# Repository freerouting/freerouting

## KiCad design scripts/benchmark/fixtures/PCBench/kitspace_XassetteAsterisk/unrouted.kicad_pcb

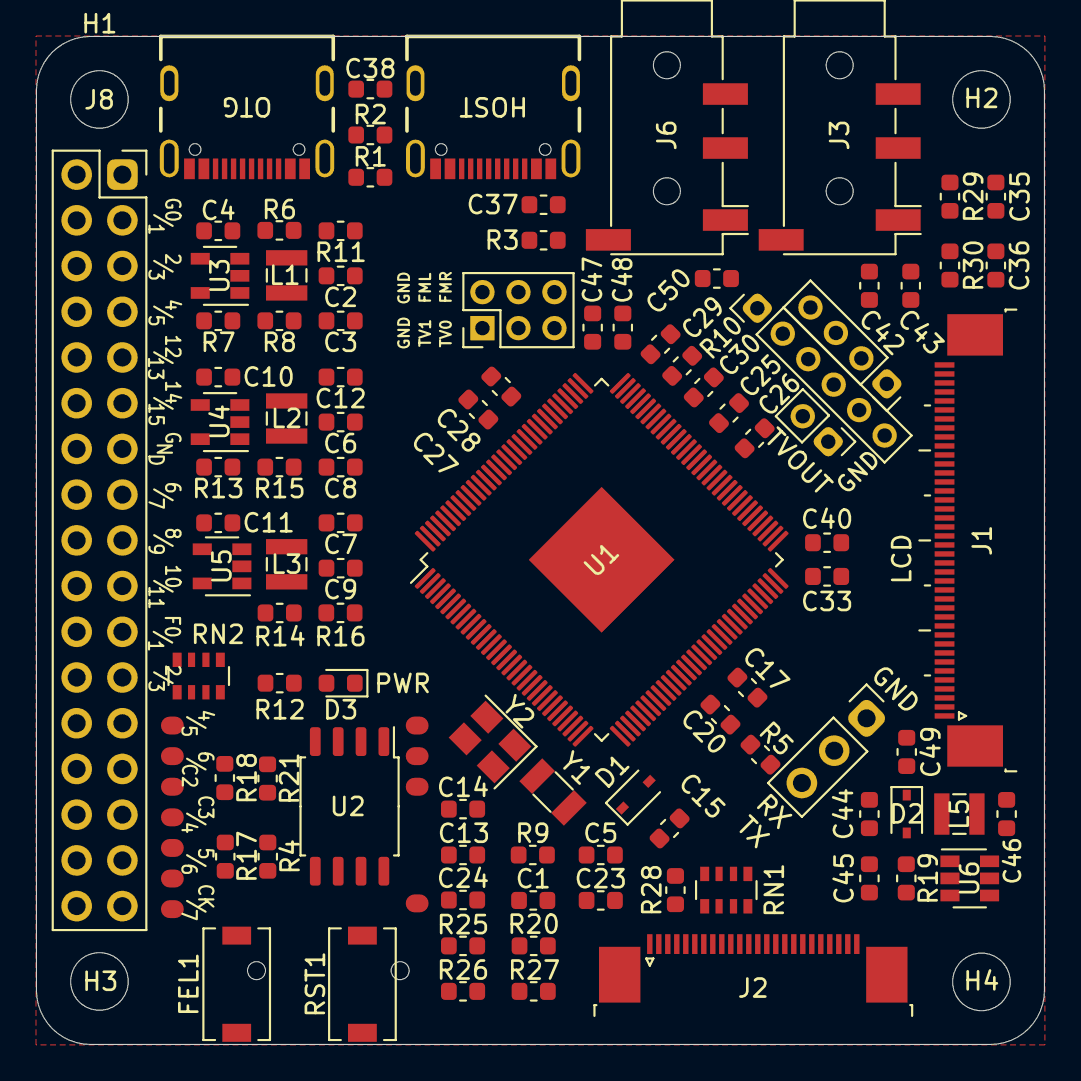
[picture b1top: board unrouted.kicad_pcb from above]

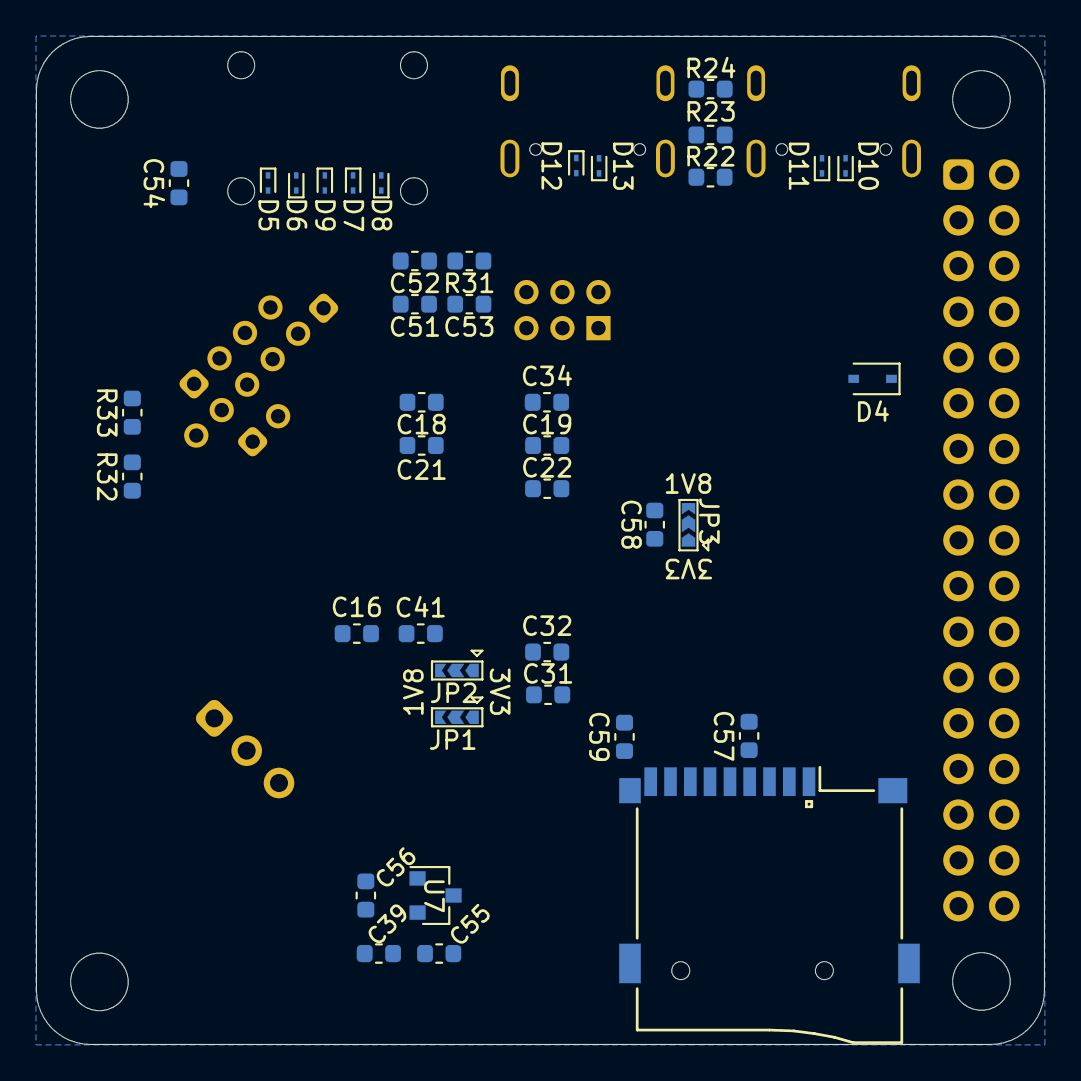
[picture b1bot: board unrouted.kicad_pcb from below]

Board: 2 copper layers, 56.0 x 56.0 mm, 145 parts (41 on the bottom side), 151 nets, no tracks yet.

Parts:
C1, C5, C13, C14: 18p; C_0603_1608Metric
C2, C4, C6, C7, C10, C11, C37, C38, C44, C46, C53, C55: 10u; C_0603_1608Metric
C3, C8, C9, C12, C15, C16, C17, C18, C19, C20, C21, C22, C23, C24, C25, C26, C31, C32, C33, C34, C35, C36, C39, C40, C41, C42, C43, C45, C47, C48, C49, C50, C51, C54, C56, C57, C58, C59: 0.1u; C_0603_1608Metric
C27, C28: 1u; C_0603_1608Metric
C29, C30: 0.47u; C_0603_1608Metric
C52: 33p; C_0603_1608Metric
D1, D2, D4: D; D_SOD-323
D3: LED; LED_0603_1608Metric
D5, D6, D7, D8, D9, D10, D11, D12, D13: ESD9B3.3ST5G; D_SOD-923
FEL1: SW_SPST; SW_SPST_EVQPE1
H1, H2, H3, H4: MountingHole; MountingHole_3.2mm_M3
H5: MountingHole_Pad; SolderWirePad_1x01_SMD_5x10mm
J1: Conn_01x40_MountingPin; TE_4-1734839-0_1x40-1MP_P0.5mm_Horizontal
J2: Conn_01x24_MountingPin; TE_2-1734839-4_1x24-1MP_P0.5mm_Horizontal
J3, J6: AudioJack4; Jack_3.5mm_PJ320D_Horizontal
J4, J5: USB4105-GF-A; GCT_USB4105-GF-A
J7: Conn_01x04; PinSocket_1x04_P2.00mm_Vertical
J8: Conn_02x17_Odd_Even; PinSocket_2x17_P2.54mm_Vertical
J9: Conn_01x06; PinHeader_1x06_P2.00mm_Vertical
J10: Conn_02x03_Odd_Even; PinHeader_2x03_P2.00mm_Vertical
J11: Conn_01x02; PinHeader_1x02_P2.00mm_Vertical
J12: Conn_01x03; PinHeader_1x03_P2.54mm_Vertical
J13: RTL8189FTV_Mod; 8189Mod
JP1, JP2, JP3: Jumper_3_Open; SolderJumper-3_P2.0mm_Open_TrianglePad1.0x1.5mm
L1, L2, L3: 2.2u; L_Wuerth_MAPI-2510
L5: 10u; L_Wuerth_MAPI-2510
R1, R2, R3, R12, R22, R23, R24: 5.1k; R_0603_1608Metric
R4, R11, R17, R18, R21, R25, R26, R27, R28, R32, R33: 10k; R_0603_1608Metric
R5: 240; R_0603_1608Metric
R6: 1k; R_0603_1608Metric
R7: 15k; R_0603_1608Metric
R8: 68k; R_0603_1608Metric
R9: 10M; R_0603_1608Metric
R10: 0; R_0603_1608Metric
R13, R16, R20: 100k; R_0603_1608Metric
R14, R15: 200k; R_0603_1608Metric
R19, R29, R30: 2R2; R_0603_1608Metric
R31: 2.2k; R_0603_1608Metric
RN1, RN2: R_Pack04; R_Array_Convex_4x0603
RST1: SW_SPST; SW_SPST_EVQPE1
Ref**: Val**; rvlogo_inv
U1: F133; LQFP-128_14x14mm_P0.4mm
U2: W25Q32JVSS; SOIC-8_5.23x5.23mm_P1.27mm
U3, U4, U5: SY8089AAAC; SOT-23-5
U6: SY7201ABC; SOT-23-6
U7: XC6206PxxxMR; SOT-23
XS1: uSD_SMD; Conn_uSDcard
Y1: Crystal; Crystal_SMD_3215-2Pin_3.2x1.5mm
Y2: 24M; Crystal_SMD_3225-4Pin_3.2x2.5mm

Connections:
+1V8: C6.1, C8.1, C17.1, C18.1, C19.1, C31.1, C32.1, C33.1, C34.1, C53.1, JP1.3, JP2.3, JP3.3, L2.1, R15.1, R31.1, U1.20, U1.26, U1.50, U1.65, U1.89, U1.97, U1.107
+3V3: C2.1, C3.1, C15.1, C24.1, C25.1, C26.1, C49.1, C55.2, C57.1, C59.1, D1.2, D4.2, J1.4, J8.2, J13.11, J13.12, J13.13, JP1.1, JP2.1, JP3.1, L1.1, R4.1, R8.1, R11.1, R12.1, R18.1, R20.1, R25.1, R27.1, R32.1, RN2.1, RN2.2, RN2.3, U1.77, U1.83, U2.8, U7.3, XS1.4
+5V: C4.1, C10.1, C11.1, C37.1, C38.1, C46.1, D4.1, J4.A4_B9, J4.B4_A9, J5.A4_B9, J5.B4_A9, J8.1, L5.1, R2.1, R3.1, R6.1, R23.1, R24.1, U3.4, U4.4, U5.4, U6.6
/CLKO: J8.33, U1.21
/CSI-AVDD: C39.1, J2.9, J2.10, U1.28
/CSI-DVDD: C56.1, J2.8, U7.2
/CSI-IOVDD: J2.23, J2.24, JP1.2, U1.34
/CSI-PWDN: J2.5, R25.2, R26.1
/CSI-RST#: J2.4, R27.2, R28.1
/DISP: J1.31, R32.2, R33.1
/DXIN: C13.2, U1.23, Y2.1
/DXOUT: C14.1, U1.22, Y2.3
/FMINL: J10.6, U1.94
/FMINR: J10.4, U1.93
/GPADC0: J9.1, U1.101
/HPOUTFB: C54.1, U1.100
/HPOUTL: C43.2, R30.2, U1.99
/HPOUTR: C42.2, R29.2, U1.98
/HS_MIC: C50.2, C52.1, D9.2, J3.S, R31.2
/LCD0-CLK: J1.30, U1.75
/LCD0-D0: J1.5, U1.86
/LCD0-D1: J1.6, U1.85
/LCD0-D2: J1.7, U1.55
/LCD0-D3: J1.8, U1.56
/LCD0-D4: J1.9, U1.57
/LCD0-D5: J1.10, U1.58
/LCD0-D6: J1.11, U1.59
/LCD0-D7: J1.12, U1.60
/LCD0-D8: J1.13, U1.84
/LCD0-D9: J1.14, U1.82
/LCD0-D10: J1.15, U1.61
/LCD0-D11: J1.16, U1.62
/LCD0-D12: J1.17, U1.63
/LCD0-D13: J1.18, U1.64
/LCD0-D14: J1.19, U1.67
/LCD0-D15: J1.20, U1.68
/LCD0-D16: J1.21, U1.80
/LCD0-D17: J1.22, U1.79
/LCD0-D18: J1.23, U1.70
/LCD0-D19: J1.24, U1.69
/LCD0-D20: J1.25, U1.71
/LCD0-D21: J1.26, U1.72
/LCD0-D22: J1.27, U1.73
/LCD0-D23: J1.28, U1.74
/LCD0-DE: J1.34, U1.76
/LCD0-HSYNC: J1.32, U1.54
/LCD0-VSYNC: J1.33, U1.53
/LCD0_PWM: U1.52, U6.4
/LCD_A: C44.1, C45.1, D2.1, J1.2, U6.5
/LCD_K: J1.1, R19.1, U6.3
/LDOB-OUT: C41.1, U1.30, U1.48, U1.49
/LINEL: C47.2, U1.96
/LINER: C48.2, U1.95
/MIC3N: C51.1, U1.88
/MIC3P: C50.1, U1.87
/NCSI0-D0: J2.22, U1.43
/NCSI0-D1: J2.21, U1.42
/NCSI0-D2: J2.20, U1.41
/NCSI0-D3: J2.19, U1.40
/NCSI0-D4: J2.18, U1.39
/NCSI0-D5: J2.17, U1.38
/NCSI0-D6: J2.16, U1.37
/NCSI0-D7: J2.15, U1.36
/NCSI0-HSYNC: RN1.7, U1.44
/NCSI0-MCLK: J12.2, RN1.5, U1.33
/NCSI0-PCLK: J12.3, RN1.6, U1.35
/NCSI0-VSYNC: RN1.8, U1.45
/PC2: J8.28, J13.6, U1.19, U2.6
/PC3: J8.29, J13.1, RN2.8, U1.18, U2.1
/PC4: J8.30, J13.3, R4.2, R17.1, U1.17, U2.5
/PC5: FEL1.2, J8.31, J13.4, R18.2, R21.1, U1.16, U2.2
/PC6: J8.32, J13.5, U1.15, U2.3
/PC7: J8.34, J13.2, U1.14, U2.7
/PF0: J8.21, U1.7, XS1.8
/PF1: J8.22, U1.8, XS1.7
/PF2: J8.23, U1.9, XS1.5
/PF3: J8.24, RN2.6, U1.10, XS1.3
/PF4: J8.25, U1.11, XS1.2
/PF5: J8.26, U1.12, XS1.1
/PF6: J8.27, RN2.7, U1.13, XS1.9
/PG0: J8.3, U1.120
/PG1: J8.4, U1.118
/PG2: J8.5, U1.119
/PG3: J8.6, U1.121
/PG4: J8.7, U1.123
/PG5: J8.8, U1.122
/PG6: J8.15, U1.1
/PG7: J8.16, U1.2
/PG8: J8.17, U1.3
/PG9: J8.18, U1.4
/PG10: J8.19, U1.5
/PG11: J8.20, U1.6
/PG12: J8.9, U1.124
/PG13: J8.10, U1.125
/PG14: J8.11, U1.126
/PG15: J8.12, U1.127
/RST: C23.1, R20.2, RST1.2, U1.27
/TP_X1: J9.2, U1.102
/TP_X2: J9.3, U1.103
/TP_Y1: J9.4, U1.104
/TP_Y2: J9.5, U1.105
/TVIN0: J10.5, U1.108
/TVIN1: J10.3, U1.109
/TVOUT: J11.2, U1.78
/TWI2-SCK: J2.3, U1.32
/TWI2-SDA: J2.2, U1.31
/USB0_N: D11.2, J4.A7, J4.B7, U1.114
/USB0_P: D10.2, J4.A6, J4.B6, U1.115
/USB1_N: D13.2, J5.A7, J5.B7, U1.113
/USB1_P: D12.2, J5.A6, J5.B6, U1.112
/VCC_PD: C40.2, JP2.2, U1.66
/VCC_PG: C58.2, JP3.2, U1.128
/VDD-CORE: C7.1, C9.1, C16.1, C20.1, C21.1, C22.1, L3.1, R16.1, U1.46, U1.51, U1.81, U1.116, U1.117
GND: C1.2, C2.2, C3.2, C4.2, C5.2, C6.2, C7.2, C8.2, C9.2, C10.2, C11.2, C12.2, C13.1, C14.2, C15.2, C16.2, C17.2, C18.2, C19.2, C20.2, C21.2, C22.2, C23.2, C24.2, C25.2, C26.2, C27.2, C28.2, C29.1, C30.1, C31.2, C32.2, C33.2, C34.2, C35.1, C36.1, C37.2, C38.2, C39.2, C40.1, C41.2, C44.2, C45.2, C46.2, C49.2, C51.2, C52.2, C53.2, C54.2, C55.1, C56.2, C57.2, C58.1, C59.2, D3.1, D5.1, D6.1, D7.1, D8.1, D9.1, D10.1, D11.1, D12.1, D13.1, FEL1.1, H5.1, J1.3, J1.29, J1.36, J1.MP, J2.1, J2.11, J2.14, J2.MP, J3.R2, J4.A1_B12, J4.B1_A12, J4.S1, J4.S2, J4.S3, J4.S4, J5.A1_B12, J5.B1_A12, J5.S1, J5.S2, J5.S3, J5.S4, J6.R2, J8.13, J8.14, J9.6, J10.1, J10.2, J11.1, J12.1, J13.7, J13.8, R1.2, R5.2, R7.2, R10.1, R13.2, R14.2, R17.2, R19.2, R21.2, R22.2, R26.2, R28.2, R33.2, RN2.4, RN2.5, RST1.1, U2.4, U3.2, U4.2, U5.2, U6.2, U7.1, XS1.6, Y2.2, Y2.4
unnamed: C1.1, R9.1, U1.24, Y1.1
unnamed: C5.1, R9.2, U1.25, Y1.2
unnamed: C12.1, R11.2, U4.1, U5.1
unnamed: C27.1, U1.111
unnamed: C28.1, U1.110
unnamed: C29.2, U1.92
unnamed: C30.2, U1.90
unnamed: C35.2, R29.1
unnamed: C36.2, R30.1
unnamed: C42.1, D6.2, J3.R1
unnamed: C43.1, D5.2, J3.T
unnamed: C47.1, D8.2, J6.R1
unnamed: C48.1, D7.2, J6.T
unnamed: D1.1, U1.29
unnamed: D2.2, L5.2, U6.1
unnamed: D3.2, R12.2
unnamed: J1.37, J7.1
unnamed: J1.38, J7.2
unnamed: J1.39, J7.3
unnamed: J1.40, J7.4
unnamed: J2.6, RN1.1
unnamed: J2.7, RN1.2
unnamed: J2.12, RN1.3
unnamed: J2.13, RN1.4
unnamed: J4.A5, R1.1, R2.2
unnamed: J4.B5, R22.1, R23.2
unnamed: J5.A5, R3.2
unnamed: J5.B5, R24.2
unnamed: L1.2, U3.3
unnamed: L2.2, U4.3
unnamed: L3.2, U5.3
unnamed: R5.1, U1.47
unnamed: R6.2, U3.1
unnamed: R7.1, R8.2, U3.5
unnamed: R10.2, U1.91
unnamed: R13.1, R15.2, U4.5
unnamed: R14.1, R16.2, U5.5

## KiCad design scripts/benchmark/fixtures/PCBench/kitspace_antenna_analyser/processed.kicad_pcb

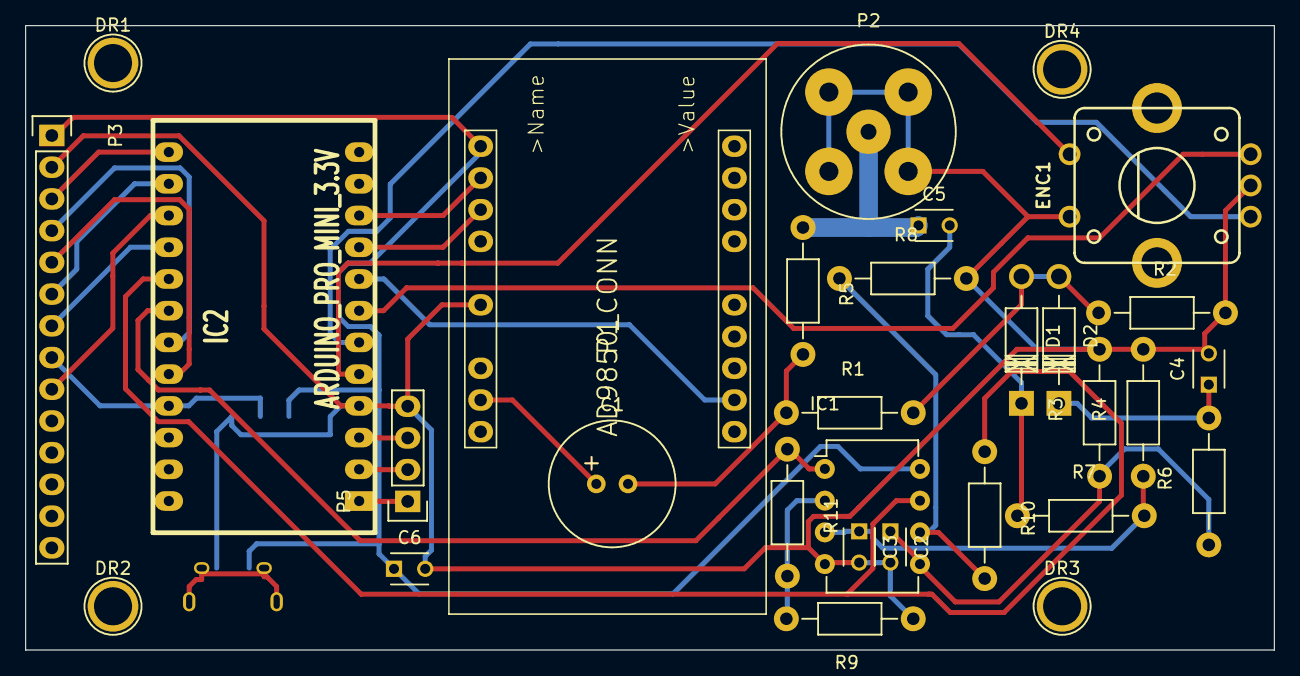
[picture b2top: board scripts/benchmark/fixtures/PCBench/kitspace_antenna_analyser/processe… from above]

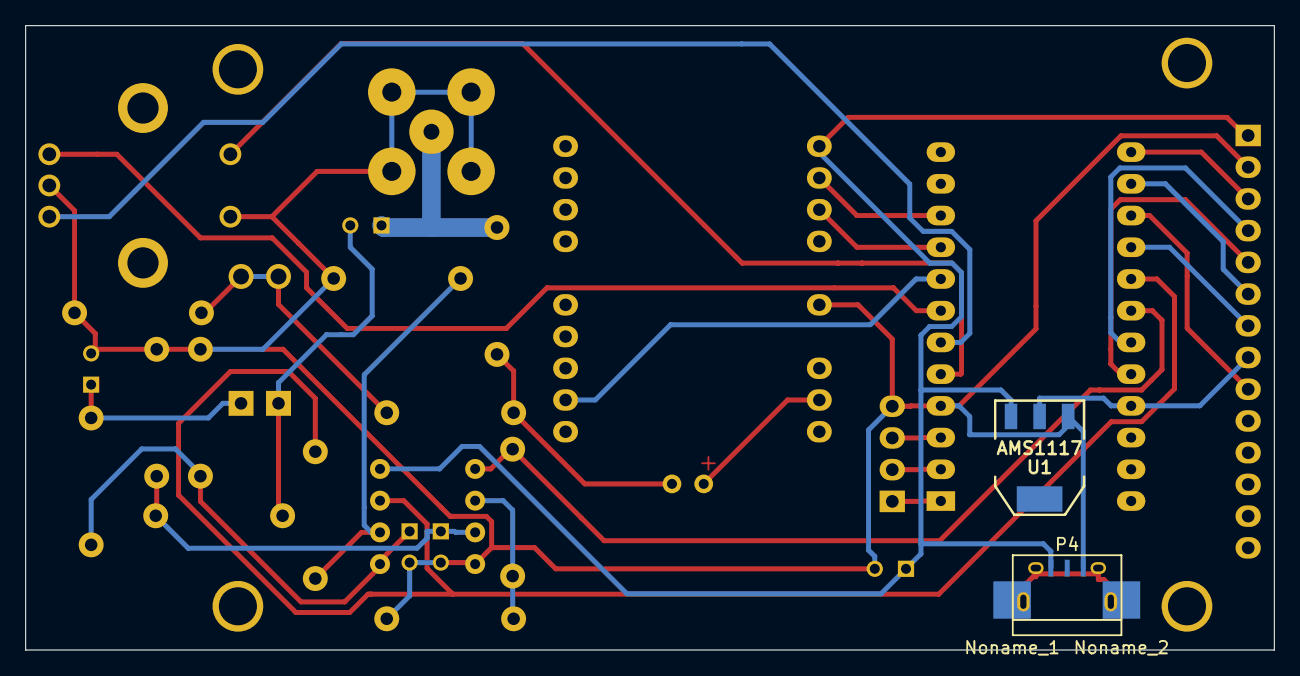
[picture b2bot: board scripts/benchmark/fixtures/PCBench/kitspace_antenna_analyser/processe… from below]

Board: 2 copper layers, 100.0 x 50.0 mm, 34 parts (4 on the bottom side), 30 nets.

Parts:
C1: 1uF; Elko_vert_20x10mm_RM2.5
C2, C3, C6: 10n; C_Disc_D3_P2.5
C4, C5: 100n; C_Disc_D3_P2.5
D1, D2: AA143; Diode_DO-41_SOD81_Horizontal_RM10
DR1, DR2, DR3, DR4: 1pin
ENC1: BI_EN11-HSM1AF15; BI_EN12-HS22AF30
IC1: MCP6002; DIP-8_W7.62mm
IC2: ARDUINO_PRO_MINI_3.3V; ARDUINO_PRO_MINI
Noname_1: S; Measurement_Point_Square-SMD-Pad_Big
Noname_2: Measurement_Point_Square-SMD-Pad_Big
P1: AD9850_CONN; DDS_AD9850
P2: BNC; bnc-ci
P3: CONN_LCD; Socket_Strip_Straight_1x14
P4: USB_OTG; USB_Micro-B
P5: CONN_PROG; Socket_Strip_Straight_1x04
R1, R2, R5: 50; Resistor_Horizontal_RM10mm
R3, R4: 100k; Resistor_Horizontal_RM10mm
R6, R7: 10k; Resistor_Horizontal_RM10mm
R8, R9: 648; Resistor_Horizontal_RM10mm
R10, R11: 5k; Resistor_Horizontal_RM10mm
U1: AMS1117; SOT223

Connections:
+5V: C6.1, IC1.8, P1.1, P3.1, P4.1, U1.3
GND: C2.2, C3.2, C4.2, C6.2, ENC1.C, ENC1.SW1, IC1.4, IC2.4, P1.6, P2.2, P3.2, P4.5, P5.4, R2.2, R3.2, R4.2, R8.2, R9.1, U1.1
unnamed: C1.1, P1.9
unnamed: C1.2, R1.1, R5.2
unnamed: C2.1, IC1.5, R3.1, R6.1
unnamed: C3.1, IC1.3, R4.1, R7.2
unnamed: C4.1, D2.1, R6.2
unnamed: C5.1, P2.1, R5.1
unnamed: C5.2, D1.1, R7.1
unnamed: D1.2, D2.2, R1.2, R2.1
unnamed: ENC1.A, IC2.6
unnamed: ENC1.B, IC2.7
unnamed: ENC1.SW2, IC2.5
unnamed: IC1.1, IC2.18, R11.1
unnamed: IC1.2, R9.2, R11.2
unnamed: IC1.6, R8.1, R10.2
unnamed: IC1.7, IC2.17, R10.1
unnamed: IC2.1, P5.1
unnamed: IC2.2, P5.2
unnamed: IC2.3, P5.3
unnamed: IC2.8, P1.12
unnamed: IC2.9, P1.3
unnamed: IC2.10, P1.2
unnamed: IC2.13, P3.3
unnamed: IC2.14, P3.6
unnamed: IC2.15, P3.9
unnamed: IC2.16, P3.7
unnamed: IC2.19, P3.4
unnamed: IC2.20, P3.5
unnamed: IC2.21, P3.8, U1.2

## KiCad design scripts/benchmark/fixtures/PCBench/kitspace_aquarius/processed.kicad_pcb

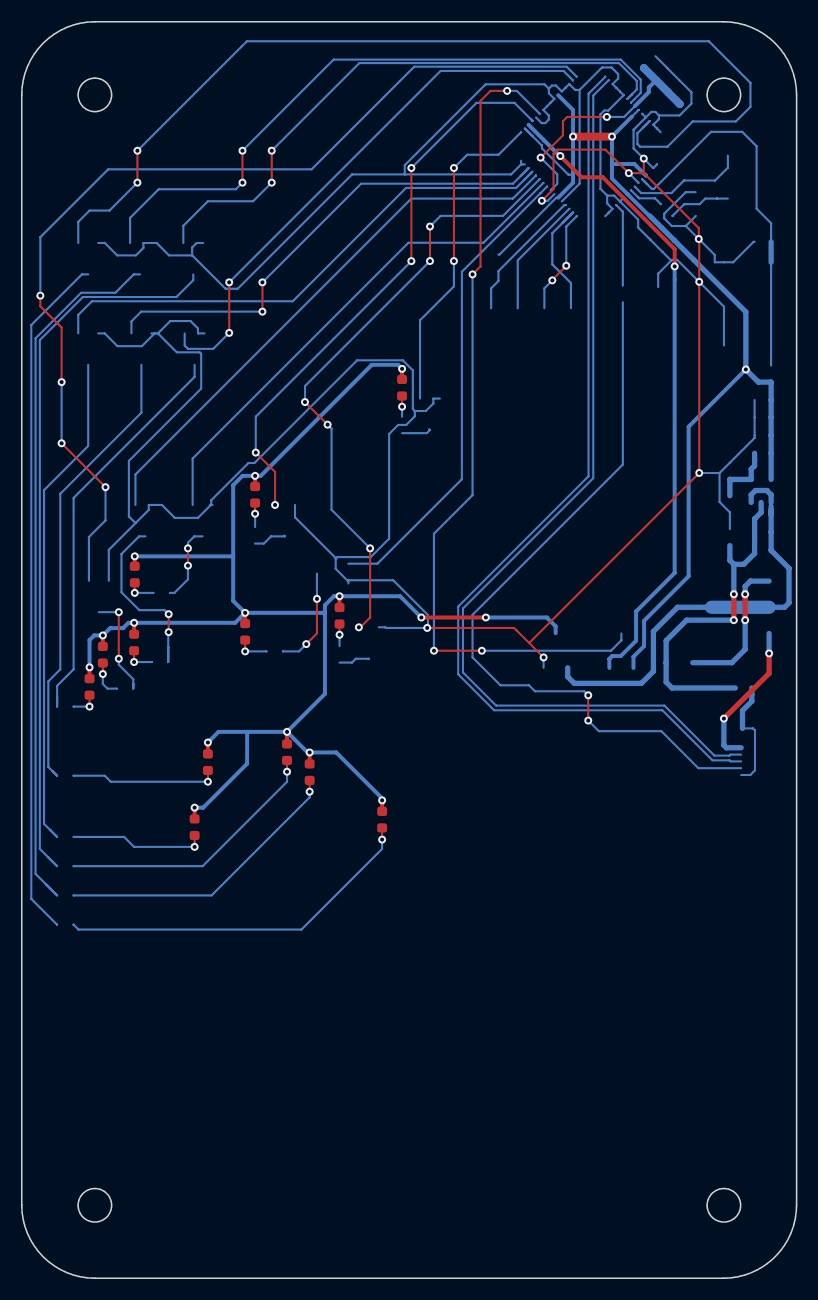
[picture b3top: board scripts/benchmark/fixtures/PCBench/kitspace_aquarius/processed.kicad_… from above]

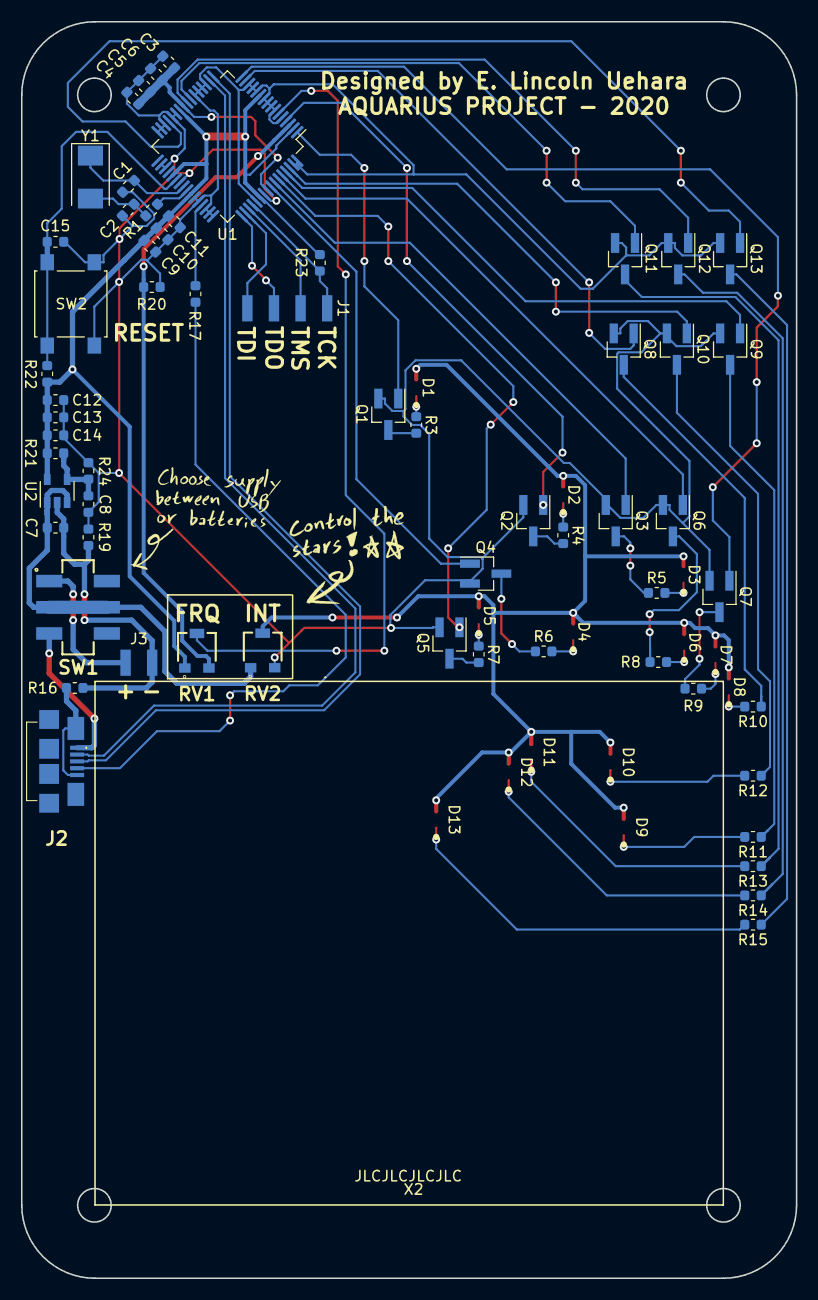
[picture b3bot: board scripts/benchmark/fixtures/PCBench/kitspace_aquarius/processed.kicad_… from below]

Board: 2 copper layers, 74.0 x 120.0 mm, 76 parts (62 on the bottom side), 63 nets.

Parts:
C1, C2: 10pF; C_0603_1608Metric
C3: 2.2uF; C_0603_1608Metric
C4, C7, C14: 1.0uF; C_0603_1608Metric
C5, C6, C10, C12, C15: 0.1uF; C_0603_1608Metric
C8, C9, C11, C13: 0.01uF; C_0603_1608Metric
D1, D2, D3, D4, D5, D6, D7, D8, D9, D10, D11, D12, D13: LED; LED_STAR_0603
J1: Conn_01x04; PinHeader_1x04_P2.54mm_SMD
J2: USB_B_Micro; ZX62B5PA33
J3: Conn_01x02; PinHeader_1x02_P2.54mm_SMD
Q1, Q2, Q3, Q4, Q5, Q6, Q7, Q8, Q9, Q10, Q11, Q12, Q13: DTC114E; SOT-23_Handsoldering
R1, R16, R17, R19, R20: 0; R_0603_1608Metric
R3, R4, R5, R6, R7, R8, R9, R10, R11, R12, R13, R14, R15: R100; R_0603_1608Metric
R21: 51k; R_0603_1608Metric
R22: 10k; R_0603_1608Metric
R23: 100k; R_0603_1608Metric
R24: 30k; R_0603_1608Metric
RV1, RV2: R_POT; PVG3A
SW1: SW_DPDT_x2; JS202011SCQN
SW2: SW_Push; SW_SPST_B3S-1000
U1: TM4C1231C3PM; LQFP-64_10x10mm_P0.5mm
U2: TPS73633DBV; SOT-23-5
X2: jlcpcb_order
X5: choose_indication
X6: control_indication
Y1: 16MHz; Crystal_SMD_Abracon_ABM3-2Pin_5.0x3.2mm

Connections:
+3V3: C9.1, C10.1, C11.1, C12.1, C13.1, C14.1, R21.1, R22.1, R23.2, RV1.1, U1.2, U1.11, U1.26, U1.37, U1.42, U1.54, U2.5
/Inputs/D+: J2.3, U1.17
/Inputs/D-: J2.2, U1.18
/Inputs/LED_PWR: D1.2, D2.2, D3.2, D4.2, D5.2, D6.2, D7.2, D8.2, D9.2, D10.2, D11.2, D12.2, D13.2, RV2.2
/Inputs/PB0: R17.2, U1.45
/Inputs/POT00: RV1.2, U1.6
/Inputs/RST: C15.1, R22.2, SW2.2, U1.38
/Inputs/TCK: J1.1, R23.1, U1.52
/Inputs/TDI: J1.4, U1.50
/Inputs/TDO: J1.3, U1.49
/Inputs/TMS: J1.2, U1.51
/Inputs/USB_PWR: J2.1, SW1.3
/Leds/Stars/LED0: Q1.1, U1.1
/Leds/Stars/LED1: Q2.1, U1.4
/Leds/Stars/LED2: Q3.1, U1.58
/Leds/Stars/LED3: Q4.1, U1.57
/Leds/Stars/LED4: Q5.1, U1.59
/Leds/Stars/LED5: Q6.1, U1.60
/Leds/Stars/LED6: Q7.1, U1.16
/Leds/Stars/LED7: Q8.1, U1.15
/Leds/Stars/LED8: Q9.1, U1.61
/Leds/Stars/LED9: Q10.1, U1.62
/Leds/Stars/LED10: Q11.1, U1.23
/Leds/Stars/LED11: Q12.1, U1.24
/Leds/Stars/LED12: Q13.1, U1.29
GNDA: R20.2, RV1.3, U1.3
GNDD: C1.2, C2.2, C3.2, C4.2, C5.2, C6.2, C8.2, C9.2, C10.2, C11.2, C12.2, C13.2, C14.2, C15.2, Q1.2, Q2.2, Q3.2, Q4.2, Q5.2, Q6.2, Q7.2, Q8.2, Q9.2, Q10.2, Q11.2, Q12.2, Q13.2, R19.2, R20.1, R24.2, RV2.3, SW2.1, U1.5, U1.7, U1.8, U1.9, U1.10, U1.12, U1.13, U1.14, U1.19, U1.20, U1.21, U1.22, U1.27, U1.28, U1.30, U1.31, U1.32, U1.34, U1.35, U1.39, U1.43, U1.44, U1.46, U1.47, U1.48, U1.53, U1.55, U1.63, U1.64
GNDPWR: C7.2, J3.2, R16.2, R19.1, U2.2
unnamed: C1.1, U1.40, Y1.1
unnamed: C2.1, R1.2, Y1.2
unnamed: C3.1, C4.1, C5.1, C6.1, U1.25, U1.56
unnamed: C8.1, R21.2, R24.1, U2.4
unnamed: D1.1, R3.2
unnamed: D2.1, R4.2
unnamed: D3.1, R5.2
unnamed: D4.1, R6.2
unnamed: D5.1, R7.2
unnamed: D6.1, R8.2
unnamed: D7.1, R9.2
unnamed: D8.1, R10.2
unnamed: D9.1, R11.2
unnamed: D10.1, R12.2
unnamed: D11.1, R13.2
unnamed: D12.1, R14.2
unnamed: D13.1, R15.2
unnamed: J2.4, R17.1
unnamed: J2.5, J2.6, R16.1
unnamed: J3.1, SW1.1
unnamed: Q1.3, R3.1
unnamed: Q2.3, R4.1
unnamed: Q3.3, R5.1
unnamed: Q4.3, R6.1
unnamed: Q5.3, R7.1
unnamed: Q6.3, R8.1
unnamed: Q7.3, R9.1
unnamed: Q8.3, R10.1
unnamed: Q9.3, R11.1
unnamed: Q10.3, R12.1
unnamed: Q11.3, R13.1
unnamed: Q12.3, R14.1
unnamed: Q13.3, R15.1
unnamed: R1.1, U1.41
VBUS: C7.1, RV2.1, SW1.2, SW1.5, U2.1, U2.3

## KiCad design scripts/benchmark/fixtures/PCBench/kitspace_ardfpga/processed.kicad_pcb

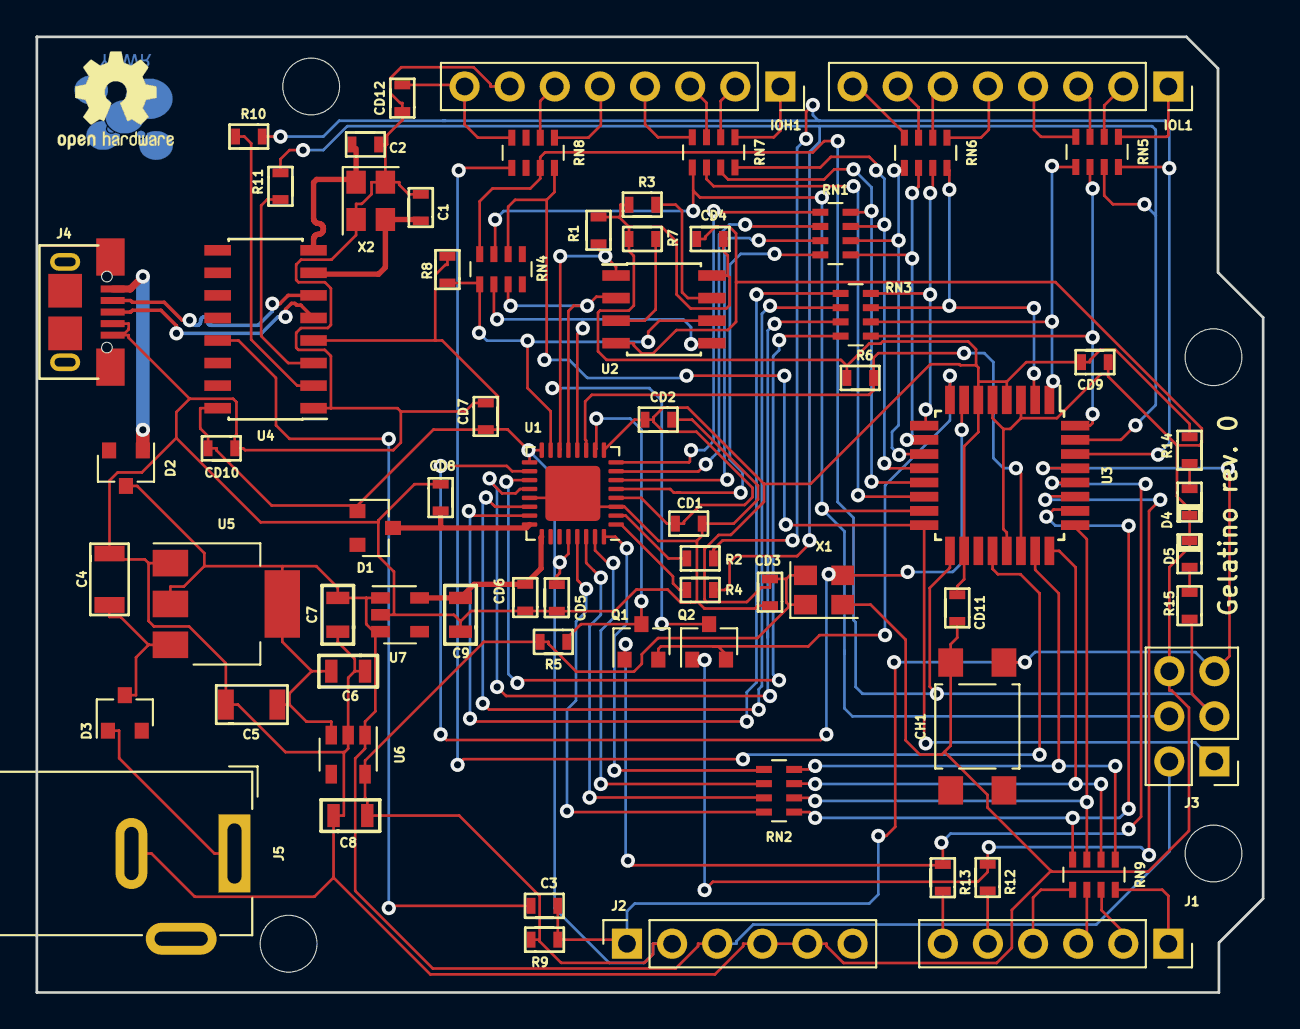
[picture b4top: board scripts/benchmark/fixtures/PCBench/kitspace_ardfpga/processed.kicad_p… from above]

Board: 2 copper layers, 69.0 x 53.8 mm, 69 parts (0 on the bottom side), 84 nets.

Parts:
C1, C2: 33pF; 0603_CAP
C3: 100nF; 0603_CAP
C4, C5: 10uF; 1206_SMD
C6, C7, C8, C9: 1uF; 0805_SMD
CD1, CD2, CD3, CD4, CD5, CD6, CD7, CD8, CD9, CD10, CD11, CD12: 100nF; 0603_CAP
CH1: RESET; SW_SPST_TL3305A
D1, D2, D3: D_Schottky_Small_ALT; SOT-23
D4, D5: LED_Small_ALT; 0603_LED
IOH1: Conn_01x08; PinSocket_1x08_P2.54mm_Vertical
IOL1: Conn_01x08; PinSocket_1x08_P2.54mm_Vertical
J1: AD; PinSocket_1x06_P2.54mm_Vertical
J2: PWR; PinSocket_1x06_P2.54mm_Vertical
J3: ICSP; PinHeader_2x03_P2.54mm_Vertical
J4: USB; USB-Micro-LCSC
J5: POWER; BarrelJack_Wuerth_6941xx301002
Q1, Q2: NMOS; SOT-23
R1, R3, R5, R6, R7, R8, R9: 10k; 0603_RES
R2, R4: 100; 0603_RES
R10, R11, R12, R13: 1k; 0603_RES
R14, R15: 220; 0603_RES
RN1, RN2, RN3, RN4: 100; R_Array_Concave_4x0603
RN5, RN6, RN7, RN8, RN9: 1k; R_Array_Concave_4x0603
U1: iCE40LP384; QFN-32-1EP_5x5mm_P0.5mm_EP3.1x3.1mm
U2: AT25xxx; SOIC-8_3.9x4.9mm_P1.27mm
U3: ATMega328; TQFP-32_7x7mm_P0.8mm
U4: CH340G; SOIC-16_3.9x9.9mm_P1.27mm
U5: AMS1117-5.0; SOT-223-3_TabPin2
U6: RT9013-33; SOT-23-5
U7: RT9013-12; SOT-23-5
X1: 16MHz; Oscillator_SMD_Abracon_ASE-4Pin_3.2x2.5mm
X2: 12 MHz; Oscillator_SMD_Abracon_ASE-4Pin_3.2x2.5mm

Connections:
+1.2V: C9.1, CD6.1, U1.25, U7.5
+3.3V: C8.1, CD1.1, CD2.1, CD3.1, CD4.1, CD5.1, CD7.1, CD9.2, CD10.1, CD11.1, D1.1, J2.2, R1.1, R3.1, R5.1, R6.1, R7.2, R8.1, R9.2, R14.2, U1.4, U1.9, U1.16, U1.17, U1.28, U2.8, U3.4, U3.6, U3.18, U4.4, U4.16, U6.5, X1.1, X1.4
+5V: C5.1, C6.1, C7.1, D2.3, J2.3, J3.2, U5.2, U6.1, U6.3, U7.1, U7.3
AD0: RN2.4, RN9.1, U3.23
AD1: RN2.3, RN9.2, U3.24
AD2: RN2.2, RN9.3, U3.25
AD3: RN2.1, RN9.4, U3.26
AD4: Q2.G, R12.1, U3.27
AD5: Q1.G, R13.1, U3.28
AREF: RN8.5, U3.20
CLK16: U1.18, U3.7, X1.3
DONE: R6.2, U1.11, U3.22
DTR: C3.1, U4.13
FRST: Q1.D, R5.2, U1.10
FSCK: R8.2, RN4.1, U1.15, U2.6
FSDI: RN4.3, U1.13, U2.2
FSDO: RN4.2, U1.12, U2.5
FSEL: Q1.S, Q2.S, U3.8
FSS: Q2.D, R1.2, U1.14, U2.1
GND: C1.1, C2.1, C4.2, C5.2, C6.2, C7.2, C8.2, C9.2, CD1.2, CD2.2, CD3.2, CD4.2, CD5.2, CD6.2, CD7.2, CD8.2, CD9.1, CD10.2, CD11.2, CD12.2, CH1.1, D4.1, D5.1, IOH1.7, J2.4, J2.5, J3.6, J4.4, J4.5, J5.2, U1.3, U1.21, U1.33, U2.4, U3.3, U3.5, U3.21, U4.1, U5.1, U6.2, U7.2, X1.2, X2.0
IO0: R2.1, R10.2, RN5.8, U3.30
IO1: R4.1, R11.2, RN5.7, U3.31
IO2: RN3.5, RN5.6, U3.32
IO3: RN3.6, RN5.5, U3.1
IO4: RN3.7, RN6.8, U3.2
IO5: RN3.8, RN6.7, U3.9
IO6: RN1.1, RN6.6, U3.10
IO7: RN1.2, RN6.5, U3.11
IO8: RN1.3, RN7.8, U3.12
IO9: RN1.4, RN7.7, U3.13
MRST: C3.2, CH1.2, J2.1, J3.5, R9.1, U3.29
MSCK: J3.3, R15.2, RN4.8, RN8.7, U3.17
MSDI: J3.1, RN4.6, RN8.8, U3.16
MSDO: J3.4, RN4.7, RN7.5, U3.15
MSS: RN7.6, U3.14
unnamed: C1.2, U4.7, X2.2
unnamed: C2.2, U4.8, X2.1
unnamed: CD8.1, D1.3, U1.24
unnamed: CD12.1, IOH1.8, RN8.4
unnamed: D2.1, J4.1
unnamed: D3.1, J5.1
unnamed: D4.2, R14.1
unnamed: D5.2, R15.1
unnamed: IOH1.1, RN7.1
unnamed: IOH1.2, RN7.2
unnamed: IOH1.3, RN7.3
unnamed: IOH1.4, RN7.4
unnamed: IOH1.5, RN8.1
unnamed: IOH1.6, RN8.2
unnamed: IOL1.1, RN5.1
unnamed: IOL1.2, RN5.2
unnamed: IOL1.3, RN5.3
unnamed: IOL1.4, RN5.4
unnamed: IOL1.5, RN6.1
unnamed: IOL1.6, RN6.2
unnamed: IOL1.7, RN6.3
unnamed: IOL1.8, RN6.4
unnamed: J1.1, RN9.8
unnamed: J1.2, RN9.7
unnamed: J1.3, RN9.6
unnamed: J1.4, RN9.5
unnamed: J1.5, R12.2
unnamed: J1.6, R13.2
unnamed: R2.2, U1.2
unnamed: R3.2, U2.7
unnamed: R4.2, U1.1
unnamed: R7.1, U2.3
unnamed: R10.1, U4.2
unnamed: R11.1, U4.3
unnamed: RN1.5, U1.8
unnamed: RN1.6, U1.7
unnamed: RN1.7, U1.6
unnamed: RN1.8, U1.5
unnamed: RN2.5, U1.32
unnamed: RN2.6, U1.31
unnamed: RN2.7, U1.30
unnamed: RN2.8, U1.29
unnamed: RN3.1, U1.23
unnamed: RN3.2, U1.22
unnamed: RN3.3, U1.20
unnamed: RN3.4, U1.19
USB_D+: J4.3, U4.5
USB_D-: J4.2, U4.6
V+: C4.1, D3.3, U5.3

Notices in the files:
scripts/benchmark/fixtures/PCBench/kitspace_aquarius/processed.kicad_pcb:
License: CC BY 4.0
